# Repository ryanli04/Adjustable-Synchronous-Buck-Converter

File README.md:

# Adjustable Synchronous Buck Converter

A synchronous buck converter built around the Analog Devices [LTC3624](https://www.analog.com/en/products/ltc3624.html) and designed in KiCad 10. The first version is a fixed 12 V to 5 V, 2 A supply. Later phases turn it into an adjustable supply with a live readout.

## Roadmap

| Phase | Goal | Status |
|---|---|---|
| 1 | Fixed 5 V / 2 A output from a 9 to 15 V input | PCB layout complete, simulation next |
| 2 | Potentiometer-adjustable output, 3 to 10 V | Planned |
| 3 | LCD showing voltage, current, power and temperature | Planned |

## Phase 1

### Specifications

| Parameter | Value |
|---|---|
| Input voltage | 9 to 15 V (12 V nominal) |
| Output | 5.0 V, 2 A max (10 W) |
| Switching frequency | 1 MHz |
| Operating mode | Pulse-skipping, for low output ripple at light load |

### Schematic

### Design highlights

- **Synchronous and monolithic:** the LTC3624 contains both power MOSFETs, so the converter needs only an inductor, capacitors and a feedback divider.
- **Output voltage:** set by R1 = 73.2 kΩ and R2 = 10 kΩ, giving V<sub>OUT</sub> = 0.6 V × (1 + R1/R2) = 4.99 V.
- **Inductor:** 4.7 µH gives about 40% ripple current at the 15 V maximum input. The Coilcraft XAL5030 is rated for 6.7 A, well above the regulator's 3.6 A maximum current limit.
- **Input protection:** the regulator's absolute maximum input is 17 V, close to the 15 V operating maximum. A 47 µF electrolytic capacitor (C1) damps the voltage spike that occurs when a supply is plugged into ceramic input capacitors.

### PCB

- 2 layers, 41.8 × 18.3 mm
- Laid out following the LTC3624 datasheet's layout guidelines: the input capacitor sits right against the VIN pins to keep the high-current switching loop small, the inductor sits directly over the SW pin, and the feedback divider is on the quiet side of the IC away from the switch node.
- All routing is on the top layer. The bottom layer is an unbroken ground plane, tied to a top-layer ground pour with stitching vias.
- Thermal vias under the IC's exposed pad carry heat into the ground plane.

### Bill of materials

| Ref | Value | Package | Part |
|---|---|---|---|
| U1 | LTC3624 buck regulator | DFN-8 3×3 mm | Analog Devices `LTC3624EDD#PBF` |
| L1 | 4.7 µH, 6.7 A saturation | 5.3 × 5.5 mm | Coilcraft `XAL5030-472MEC` |
| C1 | 47 µF 25 V aluminum electrolytic | 6.3 × 7.7 mm SMD | |
| C2 | 10 µF 25 V X7R | 1206 | |
| C3 | 2.2 µF 10 V X7R | 0805 | |
| C4 | 47 µF 16 V X5R/X7R | 1210 | |
| R1 | 73.2 kΩ 1% | 0805 | |
| R2 | 10 kΩ 1% | 0805 | |
| R3 | 100 kΩ (power-good pull-up) | 0805 | |
| J1, J2 | 2-position screw terminal, 5.08 mm | | Phoenix Contact `1715721` |

## Repository structure

```
images/                          Renders and schematic used in this README
Buck_Converter/
  Buck_ConverterV1/
    Buck_ConverterV1.kicad_pro   KiCad project
    Buck_ConverterV1.kicad_sch   Schematic
    Buck_ConverterV1.kicad_pcb   PCB layout
    Buck_ConverterNew.kicad_sym  Project symbol library
    footprints.pretty/           Vendor LTC3624 footprints
```

## References

- [LTC3624 datasheet](https://www.analog.com/media/en/technical-documentation/data-sheets/36242fd.pdf)
- [Coilcraft XAL50xx inductor datasheet](https://www.coilcraft.com/getmedia/49bc46c8-4b2c-45b9-9b6c-2eaa235ea698/xal50xx.pdf)

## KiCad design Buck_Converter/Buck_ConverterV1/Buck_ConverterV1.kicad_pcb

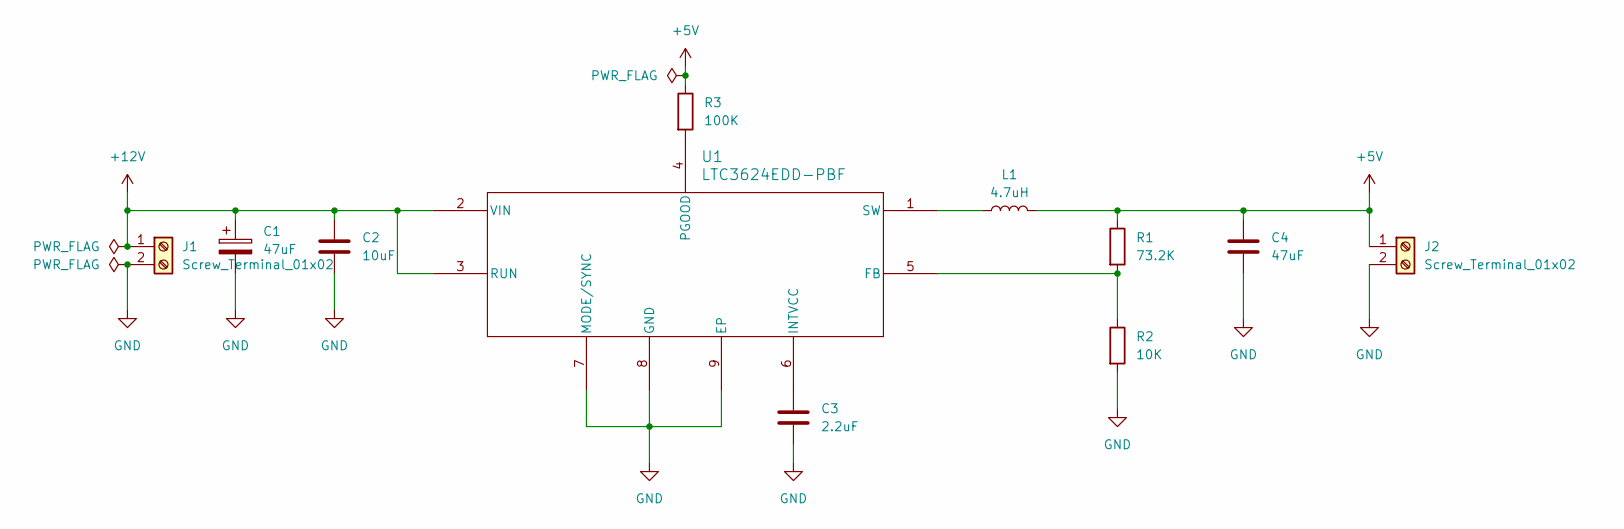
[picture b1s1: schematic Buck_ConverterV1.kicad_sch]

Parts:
C1: 47uF; CP_Elec_6.3x7.7
C2: 10uF; C_1206_3216Metric
C3: 2.2uF; C_0805_2012Metric
C4: 47uF; C_1210_3225Metric
J1, J2: Screw_Terminal_01x02; TerminalBlock_Phoenix_MKDS-1,5-2-5.08_1x02_P5.08mm_Horizont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
L1: 4.7uH; L_Coilcraft_XAL5030-XXX
R1: 73.2K; R_0805_2012Metric
R2: 10K; R_0805_2012Metric
R3: 100K; R_0805_2012Metric
U1: LTC3624EDD-PBF; DFN-8-1EP_3x3mm_P0.5mm_EP1.66x2.38mm

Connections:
+5V: C4.1, J2.1, L1.2, R1.1, R3.1
+12V: C1.1, C2.1, J1.1, U1.2 (VIN), U1.3 (RUN)
GND: C1.2, C2.2, C3.2, C4.2, J1.2, J2.2, R2.2, U1.7 (MODE/SYNC), U1.8 (GND), U1.9 (EP)
unnamed: R1.2, R2.1, U1.5 (FB)
unnamed: C3.1, U1.6 (INTVCC)
unnamed: R3.2, U1.4 (PGOOD)
unnamed: L1.1, U1.1 (SW)

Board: 2 copper layers, 11 parts (0 on the bottom side), 7 nets, no tracks yet.
